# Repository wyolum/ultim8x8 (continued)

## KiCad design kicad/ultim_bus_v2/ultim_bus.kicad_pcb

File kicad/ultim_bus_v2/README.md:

# ultim_bus

A PCB "bus bar" to allow three ultim8x8 modules to be connected easily. Mouse bites allow it to be snapped off easily. With some imagination, can be used to expand to larger matrices.

The first panel can be populated with a Feather M0. There are six SMD switches connected to A0 through A5 on the Feather M0, with pull up resistors (SMD 0805). Switch functions can be arbitrarily assigned in code.

License
-------
[CERN Open Hardware Licence v1.2 ]

[CERN Open Hardware Licence v1.2 ]:http://www.ohwr.org/attachments/2388/cern_ohl_v_1_2.txt

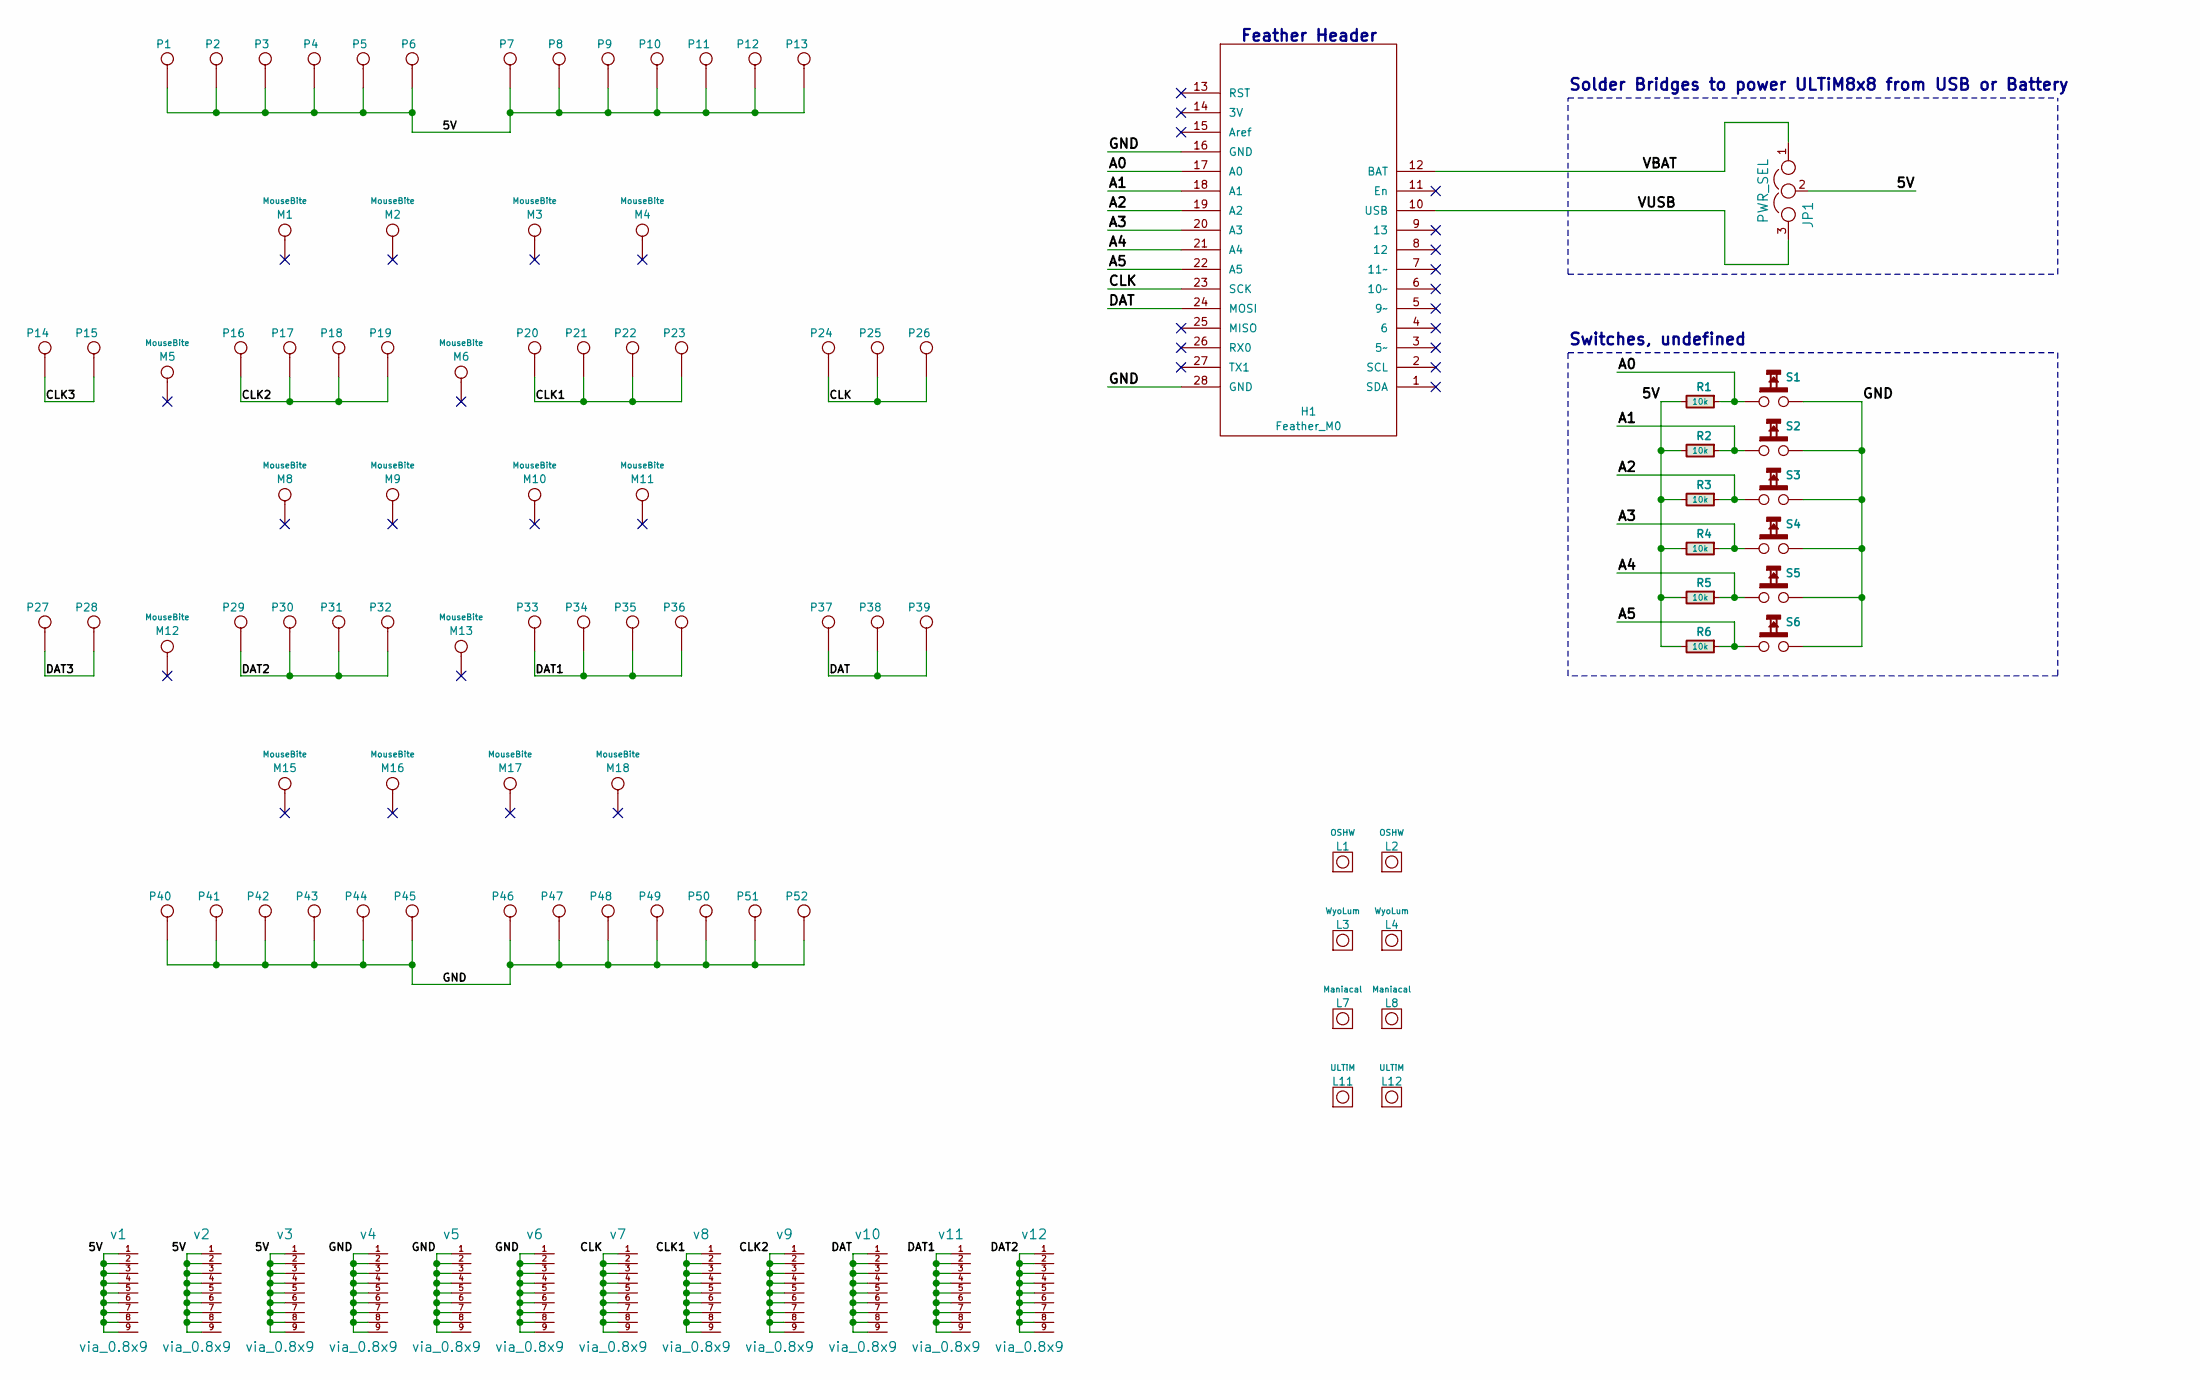
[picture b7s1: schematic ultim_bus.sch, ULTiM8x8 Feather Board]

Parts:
H1: Feather_M0; FEATHER_M0_2
JP1: PWR_SEL; switch_spdt
L1, L2: OSHW; OSHW_6mm
L3, L4: WyoLum; logo_wyo_butterfly_small
L7, L8: Maniacal; logo_MLlabs_small
L11, L12: ULTiM; logo_ultim8x8_small
M1, M2, M3, M4, M8, M9, M10, M11, M15, M16, M17, M18: MouseBite; mouse-bite-5.08mm-slot
M5, M6, M12, M13: MouseBite; mouse-bite-2.54mm-slot
P1, P4, P5, P8, P9, P12, P15, P16, P19, P20, P23, P24, P28, P29, P32, P33, P36, P37, P40, P43, P44, P47, P48, P51: CONN_1; Screw_SqPad
P2, P3, P6, P7, P10, P11, P13, P14, P17, P18, P21, P22, P25, P26, P27, P30, P31, P34, P35, P38, P39, P41, P42, P45, P46, P49, P50, P52: CONN_1; Screw
R1, R2, R3, R4, R5, R6: 10k; r_0805
S1, S2, S3, S4, S5, S6: SPST-M-2; SW_SMD
v1, v2, v3, v4, v5, v6, v7, v8, v9, v10, v11, v12: via_0.8x9

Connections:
/5V: JP1.2, P1.1, P2.1, P3.1, P4.1, P5.1, P6.1, P7.1, P8.1, P9.1, P10.1, P11.1, P12.1, P13.1, R1.2, R2.2, R3.2, R4.2, R5.2, R6.2, v1.1, v1.2, v1.3, v1.4, v1.5, v1.6, v1.7, v1.8, v1.9, v2.1, v2.2, v2.3, v2.4, v2.5, v2.6, v2.7, v2.8, v2.9, v3.1, v3.2, v3.3, v3.4, v3.5, v3.6, v3.7, v3.8, v3.9
/A0: H1.17 (A0), R1.1, S1.1
/A1: H1.18 (A1), R2.1, S2.1
/A2: H1.19 (A2), R3.1, S3.1
/A3: H1.20 (A3), R4.1, S4.1
/A4: H1.21 (A4), R5.1, S5.1
/A5: H1.22 (A5), R6.1, S6.1
/CLK: H1.23 (SCK), P24.1, P25.1, P26.1, v7.1, v7.2, v7.3, v7.4, v7.5, v7.6, v7.7, v7.8, v7.9
/CLK1: P20.1, P21.1, P22.1, P23.1, v8.1, v8.2, v8.3, v8.4, v8.5, v8.6, v8.7, v8.8, v8.9
/CLK2: P16.1, P17.1, P18.1, P19.1, v9.1, v9.2, v9.3, v9.4, v9.5, v9.6, v9.7, v9.8, v9.9
/CLK3: P14.1, P15.1
/DAT: H1.24 (MOSI), P37.1, P38.1, P39.1, v10.1, v10.2, v10.3, v10.4, v10.5, v10.6, v10.7, v10.8, v10.9
/DAT1: P33.1, P34.1, P35.1, P36.1, v11.1, v11.2, v11.3, v11.4, v11.5, v11.6, v11.7, v11.8, v11.9
/DAT2: P29.1, P30.1, P31.1, P32.1, v12.1, v12.2, v12.3, v12.4, v12.5, v12.6, v12.7, v12.8, v12.9
/DAT3: P27.1, P28.1
/GND: H1.16 (GND), H1.28 (GND), P40.1, P41.1, P42.1, P43.1, P44.1, P45.1, P46.1, P47.1, P48.1, P49.1, P50.1, P51.1, P52.1, S1.2, S2.2, S3.2, S4.2, S5.2, S6.2, v4.1, v4.2, v4.3, v4.4, v4.5, v4.6, v4.7, v4.8, v4.9, v5.1, v5.2, v5.3, v5.4, v5.5, v5.6, v5.7, v5.8, v5.9, v6.1, v6.2, v6.3, v6.4, v6.5, v6.6, v6.7, v6.8, v6.9
/VBAT: H1.12 (BAT), JP1.1
/VUSB: H1.10 (USB), JP1.3

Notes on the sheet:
Solder Bridges to power ULTiM8x8 from USB or Battery
Feather Header
Switches, undefined

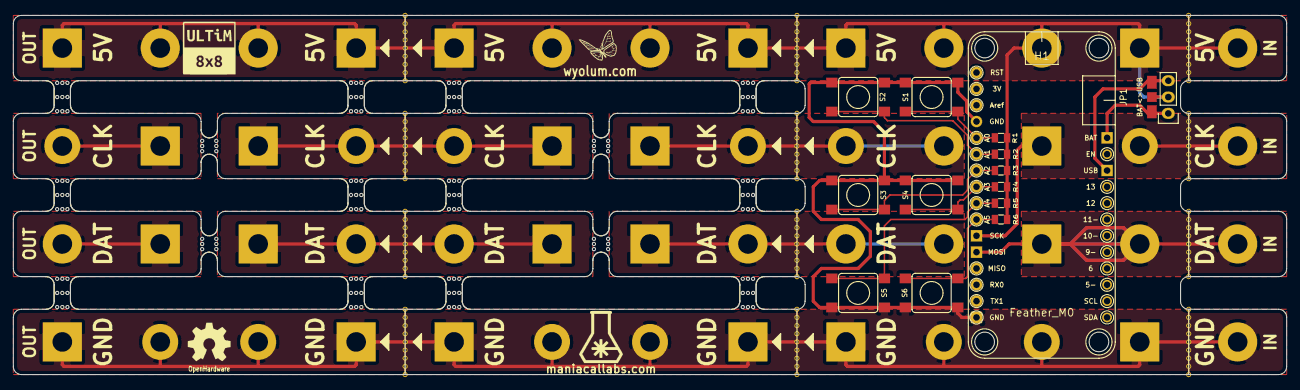
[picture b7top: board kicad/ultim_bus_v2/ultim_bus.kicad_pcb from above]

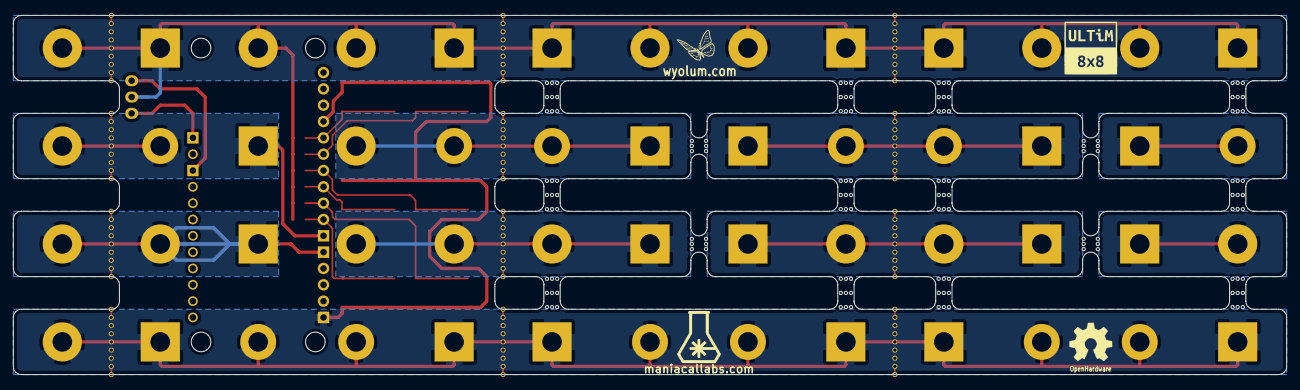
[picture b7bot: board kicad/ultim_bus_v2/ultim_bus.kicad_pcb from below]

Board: 2 copper layers, 198.1 x 55.9 mm, 102 parts (4 on the bottom side), 18 nets.

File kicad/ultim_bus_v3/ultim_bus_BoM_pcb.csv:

Id;Designator;Package;Quantity;Designation;Supplier and ref
1;M13,M6;mouse-bite-2.54mm-slot;2;MouseBite;
2;L8,L7;logo_MLlabs_small;2;LOGO_ML;
3;P31,P38,P35,P34,P30,P27,P2,P3,P6,P7,P10,P11,P14,P17,P18,P21,P22,P25,P41,P42,P45,P46,P49,P50;Screw;24;CONN_1;
4;L4,L3;logo_wyo_butterfly_small;2;LOGO_WL;
5;L11,L12;logo_ultim8x8_small;2;LOGO_U88;
6;L2,L1;OSHW_6mm;2;OSHW;
7;P1,P4,P5,P8,P9,P12,P28,P29,P32,P33,P36,P37,P15,P16,P19,P20,P23,P24,P40,P43,P44,P47,P48,P51;Screw_SqPad;24;CONN_1;
8;M2,M9,M16;mouse-bite-5.08mm-slot;3;MouseBite;
9;JP1;switch_spdt;1;PWR_SEL;
10;v1,v2,v3,v4,v5,v6,v7,v8,v9,v10,v11,v12,v13,v14,v15,v16;via_0.8x9;16;via_0.8x9;
11;M3,M4,M10,M11,M17,M18;mouse-bite-5.08mm-slot;6;MouseBite;
12;H1;FEATHER_M0_2;1;Feather_M0;
13;S2,S1,S3,S4,S5,S6;SW_SMD;6;SPST-M-2;
14;R6,R5,R4,R3,R2,R1;r_0805;6;10k;

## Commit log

2016-02-18 UlTiM8x8 board layout complete
2016-02-18 UlTiM8x8 board layout complete. Gerbers ready. ULTiM_bus mockup
2016-02-19 UlTiM8x8 board layout complete, Gerbers ready for fab
2016-02-19 UlTiM_bus layout, gerber complete. Bus accessory for ULTiM8x8
2016-02-19 Adding beggining of pricing breakdown
2016-02-21 Removed digikey pricing from BOM
2016-02-23 UlTiM8x8 fresh layout with new geometry
2016-02-24 revised layout, final. Gerbers ready for fab
2016-02-25 added magnetic assembly concept drawings
2016-03-17 Power Stud 3D model added in fabricate
2016-03-17 45 deg angled layout
2016-03-18 angled LED version complete
2016-03-18 added ULTiM8x8 angled LED .step Model
2016-03-18 new ULTiM_bus layout
2016-03-19 ULTiM_bus redesign
2016-03-22 final gerbers ready
2016-03-23 updated to 20mm standoffs
2016-08-10 added module positions files
2016-09-08 ultim cube assembly, WIP
2016-09-09 ultim8x8 cube idea,WIP
2016-09-09 add LED counting OpenCV script
2016-09-10 single panel stand for testing
2016-09-10 fix hex recesses in single panel stand
2016-09-10 fixed KiCad version issue
2016-09-10 added test software
2016-09-10 added test document
2016-09-11 added FontTest sketch
2016-09-13 updated 2x6 backplane
2016-09-13 updated backplane
2016-09-14 edited TestFirmware.ino to allow >255 LEDs
2016-09-16 cube core work in progress
2016-09-16 added Display test demo
2016-09-16 git hell fix
2016-09-18 cube WIP
2016-09-19 made font constants
2016-09-29 made more backplane size choices
2016-09-29 removed extra stuff from 2x7 backplane
2016-09-30 Fixed TestFirmware.ino for dual M0/328 compatiblilty
2016-09-30 added file save options to bitmap editor
2016-10-01 added comments to bitmap_editor.py
2016-10-01 added toolspython bitmap_editor.py !
2016-10-15 modified 3D support cube design
2016-10-24 adding updated sequencer
2016-10-25 copied bitmap_editor.py to scripts/PixelPainter.py
2016-11-05 Initial commit of Ultim8x8 Feather Board
2016-11-05 Removed specific reference to HUZZAH feather (any Feather should work)
2016-11-12 added another example to RF24 library
2016-11-12 added RF24 library
2016-11-12 added rest of RF24 lib
2016-11-12 minor bugfix
2016-11-12 only ack packets for me
2016-11-21 add single panel template, and 3x3 template
2016-11-26 changing pin strip to sockets for 3D model
2016-12-04 adding featherboard case
2016-12-04 orgainzed file structure
2016-12-14 adding ESP8266 firmware and painter test
2016-12-14 simplifying test.py
2016-12-14 adding multi demo
2016-12-18 adding FastLED and ESP WiFi manager
2016-12-18 fixing WiFiUdp case sensitivity issue on linux
2016-12-18 commented out annoying messages from FastLED
2016-12-25 belt buckle 3D case
2016-12-31 archived old kicad design in _old folder
2016-12-31 board outline changed. upgraded 3 pin headers to 4 pins
2016-12-31 rotated 4 pin headers by 45 deg
2016-12-31 v2 of Feather carrier board
2017-01-02 timeout for network status and now supports 4 displays
2017-01-02 clean up
2017-01-03 feather_v2 added SMD shorting links and extra power switch
2017-01-07 bugfix, n_row, n_col in PixelPianter()
2017-01-07 works for multipanel with painter
2017-01-10 add io panel example
2017-01-12 BoM update
2017-01-15 fresh 3D CAD render files
2017-01-15 readme edit
2017-01-15 minor edit
2017-01-16 README edits
2017-02-05 added BLEhat and support
2017-02-05 troubleshooting BLEhat
2017-02-06 switched data and clock to SDA and SCL to work with ble feather m0
2017-03-05 updated puzzle test
2017-03-18 started race timer code, tested FastLED support
2017-03-19 feather board adapter v3
2017-04-02 ultim_bus_v2 now includes M0 header
2017-04-03 added 6 SMD switches to ultim_bus_v2 with pullup resistors
2017-04-03 ultim_bus_v2 gerber generated
2017-04-03 clean up of all kicad project folders
2017-04-06 Upgraded DisplayTest to FastLED: DisplayFast
2017-04-07 working on font library for pixel displays
2017-04-08 work in progress, ULTiM_cube assembly
2017-04-09 CubeClock work in progress ultim8x_assy_idea2
2017-04-09 added test for ULTiMBus (8x24) array
2017-04-09 ultim_bus rev 3 modular, stackable
2017-04-09 cube rev2 work in progress STL DXF SVG ready for trial
2017-04-09 added images for cube clock rev2
2017-04-10 corrections and cleanup
2017-04-15 better ultim_bus images
2017-04-17 cube ver2 improvements
2017-04-19 added AllPixel ish code
2017-04-19 ULTiM8_bus BoM added
2017-04-25 added dice simulation for ULTiM8x8x6 cube.
2017-04-25 added BP Serial Receiver
2017-04-25 Somehow RTClib files where overwritten in a BoM update. Restored to prev
2017-04-25 trimmed all extra data from ULTiM8_Die/ so that it would fit in UNO memory
2017-04-25 cleanup
2017-04-28 minor mods to Belt BuckleCAD
2017-05-06 Bus Bar PCB added El. Cap, removed short to GND
2017-05-07 ported Jason Coon's esp8266-fastled-webserver, a fast LED demo
2017-05-07 changed autoplayDuration to 3
2017-05-07 commented out line causes crash. problem with gGradiantPaletteCount
2017-05-07 added a couple demos
2017-05-08 added esp8266-fastled-webserver
2017-05-09 Removed unused Commands.h, updated FastLED library.
2017-05-09 More FastLED demo improvements
    Working on fire & water, better but still not quite right.
    Increased palette and autoplay durations.
    Removed more unused code.
2017-05-09 removed debug prints in fastled-demo.ino
2017-05-13 updated esp code
2017-05-13 added arduinoWebSockets
2017-05-14 add pixel mapping for 24x24
2017-05-14 added mapping file MatrixMaps.h for mamy ULTIM*x* sizes
2017-05-14 moved MatrixMaps
2017-05-14 nother MatrixMaps update
2017-05-14 put back Map.h
2017-05-14 commented out Cube animations
2017-05-18 moving files from messed up copy
2017-05-18 adding files
2017-05-18 added ultim_bus_conn -- an inter bus connector strip
2017-05-23 pushing SunRiseClock updates
2017-06-13 changed color scheme - black mask, white legend
2017-06-14 ultim_bus v4 changed switches to thru hole
2017-06-14 ultim_bus v3 image files rename
2017-07-14 added h files to SunRiseClock
2017-07-17 added NTP functions to SunRiseClock
2017-07-18 added clock display code to SunRise Clock
2017-07-20 added MatrixMaps lib
2017-07-20 added new sunrise visualiztions
2017-07-23 integreated NTP time request into SunRiseClock
2017-07-23 updated time initialization on SunRiseClock
2017-07-23 added SPIFFS data to SunRiseClock
2017-07-24 added SunRiseClock scad files and svgs
2017-07-24 more sunriseclock scad files
2017-07-29 added timezone field, change data type of Field.value to int16 to allow negative numbers
2017-07-29 added alarm boolean to interface
2017-08-02 added alarm_hour and alarm_min to SunRiseClock web interface
2017-08-03 integrated alarm functions into SunRiseClock
2017-08-03 alarm now turns power on when it activates
2017-08-03 bug fixes on SunRiseClock Alarm
2017-08-03 added esp8266-fastled-webserver-clock/
2017-08-04 Changed FLIP_DISPLAY to use MatrixWidth and MatrixHeight. Added gitignore to prevent publishing credentials.
2017-08-04 added color patterns to clock display
2017-08-04 added ultim8x48 matrix map
2017-08-04 turned clock() into just a mask on top of what ever pattern you choose, added display_clock to interface
2017-08-04 bug fix to alarm acivation to turn display_clock off
2017-08-04 now pattern and brightness are saved when alarm activates
2017-08-09 add feather huzzah footprint
2017-08-10 ultim bus v5 for Huzzah
2017-08-10 edited readme
2017-08-10 ultim_bus_v5 swappes S1 and S2
2017-08-10 modified switch 3d module
2017-08-10 U88 ver2 with extra power / signal mounting holes
2017-08-11 added some missing files
2017-08-12 added missing font file
2017-08-12 add demo reel for ultim8x8 settings
2017-08-13 added mDNS library
2017-08-19 U88 connector strip PCB update
2017-08-20 made pixel_maps.py easily extensible to any number of 8x8 rows cols
2017-08-28 added eBumper folder in fabricate
2017-08-31 added 8x8 font
2017-09-03 Upgraded PixelPainter to python3
2017-09-03 added py2 version of PixelPainter.py
2017-09-03 add non-matrix, simple pixelsetting test
2017-09-04 Updated README to comment out lines
2017-09-15 STFU enclosure mods
2017-09-17 STFU enclosure update
2017-09-17 updated STFU enclosure in eBumper
2017-09-21 STFU case updated
2017-09-21 STFU enclosure updated
2018-01-17 8bit/single row clock-- someday merge into main
2018-01-19 added ultim_bus snapped off 3D files
2018-02-19 added 3x7x8x8 backplane
2018-03-18 added multi feather pinout diagram
2018-11-16 added center point to PixelPainter.py
2019-05-29 added 1x12 enclosure design
2019-07-14 added EMDR code to examples
2019-07-14 Take A Number
2019-07-28 added TakeANumber
2019-07-28 add simpleNumber
2019-07-28 doubled matrix width for two-sidedness
2019-07-28 added API functions
2019-07-28 websockets API for simplenumber
2019-07-28 add simple websocket button code
2019-07-30 IncrementButton mods
2019-08-18 added ultim_bus pinout
2019-08-21 adding esp8266 clock code
2019-08-22 added pubsubcleint
2019-08-22 added pubsub client support files
2019-08-28 added BasicHttpClient example
2019-08-29 added Time.h lib
2019-08-29 added EEPROMAnything
2019-08-29 added NTPClient
2019-08-31 added moon phases to WyoBean
2019-08-31 added enclosure for wyobean
2019-09-01 adding hangers to WyoBean
2019-09-01 wyobean enclosure...
2019-09-01 added hanger.FCStd
2019-09-01 working on hanger w/ anool
2019-09-01 hanger.stl
2019-09-02 added 3d printed guide for wall mounting
2019-09-12 added DuPPaLib for I2CNavKey
2019-09-12 added Dulles clock with navkey
2019-09-14 DullesNavKey touch
2019-09-14 removed unneeded funtion in DullesNavKey
2019-09-30 added Snake
2019-09-30 added Snake.h to WyoBean
2019-09-30 added fonts file
2019-09-30 snake.ino
2019-10-09 corrected 12 hr format
2019-10-18 added nav key connection diagram
2019-12-28 ifdefed out navkey code to DullesNavKey
2022-12-24 added stripped down clock for hearsh called DesKlok
2024-03-06 updated ultimbus pinout
2024-03-12 fixed ultimbus pinout diagram
